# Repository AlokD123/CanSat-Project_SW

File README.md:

# README #

This is the flight software for the Carleton University CanSat team, primarily for the 2015 competition. Full details about the Int'l CanSat Competition may be found [here](http://www.cansatcompetition.com/). Note that the contents of this repository were migrated from a private Bitbucket repository which was used at the time of the competition, so author attributions are shown at the tops of files in lieu of a commit history.

### What is this repository for? ###

The Flight_SW directory contains all the required code to build and deploy the firmware for the CanSat Science Vehicle designed in 2014/2015. The GroundStation_SW directory contains the code to run a ground station GUI. The Flight_HW directory contains sample schematics, layouts, and images of PCBs designed for the competition.

### How do I get set up? ###

This software is written with CodeWarrior for MCUs (Special Edition). It is targeting a custom PCB with the MKL16Z.
In order to program the board in that IDE (not just debug it) you must go under Project->Properties->C/C++ Build->Settings->Librarian and change Model to ewl.

### Where can I find more details about the project? ###
Refer to the Critical Design Review (CDR) document: https://github.com/AlokD123/CanSat-Project_SW/blob/master/Cansat2015_1001_CDR_v01.pdf

For brevity, two concept images are shown below. The top image is the Concept of Operations for the competition. The bottom image is a block diagram of the can-sized satellite's electronics.

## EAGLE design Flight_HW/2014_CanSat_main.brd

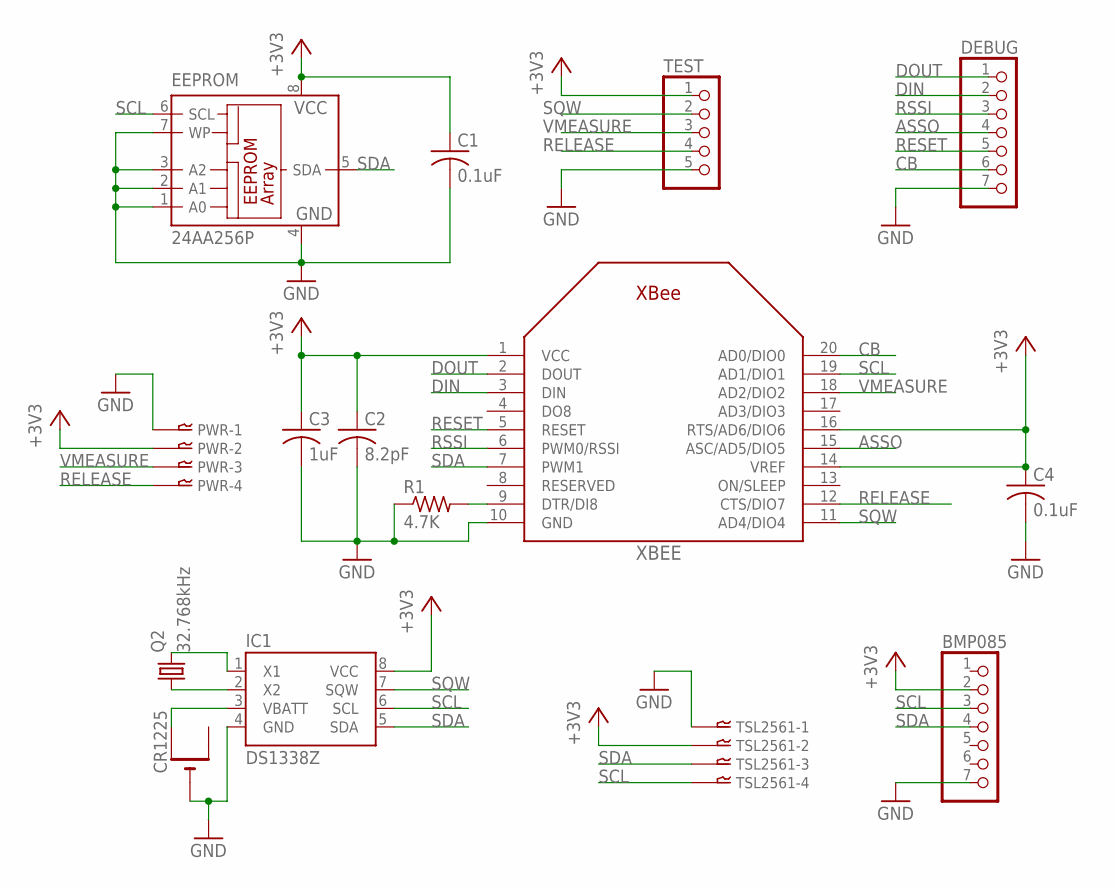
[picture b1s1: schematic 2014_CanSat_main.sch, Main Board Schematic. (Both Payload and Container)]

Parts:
BMP085: PINHD-1X7; 1X07
C1, C4: 0.1uF; C050-024X044
C2: 8.2pF; C050-024X044
C3: 1uF; C050-024X044
CR1225: CR1220THM; CR1220-THM
DEBUG: PINHD-1X7; 1X07
EEPROM: 24AA256P; DIL8
IC1: DS1338Z; SO08
PWR: 04-JST-B4B-XH-A; B4B-XH
Q2: 32.768kHz; TC26H
R1: 4.7K; 0309/10
TEST: PINHD-1X5; 1X05
TSL2561: 04-JST-B4B-XH-A; B4B-XH
XBEE: XBEE

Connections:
+3V3: BMP085.2, C1.1, C2.1, C3.1, C4.1, EEPROM.8 (VCC), IC1.8 (VCC), PWR.P$2, TEST.1, TSL2561.P$2, XBEE.1 (VCC), XBEE.14 (VREF), XBEE.16 (RTS/AD6/DIO6)
ASSO: DEBUG.4, XBEE.15 (ASC/AD5/DIO5)
CB: DEBUG.6, XBEE.20 (AD0/DIO0)
DIN: DEBUG.2, XBEE.3 (DIN)
DOUT: DEBUG.1, XBEE.2 (DOUT)
GND: BMP085.7, C1.2, C2.2, C3.2, C4.2, CR1225.-, DEBUG.7, EEPROM.1 (A0), EEPROM.2 (A1), EEPROM.3 (A2), EEPROM.4 (GND), EEPROM.7 (WP), IC1.4 (GND), PWR.P$1, R1.1, TEST.5, TSL2561.P$1, XBEE.10 (GND)
unnamed: R1.2, XBEE.9 (DTR/DI8)
unnamed: IC1.2 (X2), Q2.1
unnamed: IC1.1 (X1), Q2.2
unnamed: CR1225.+1 (+), IC1.3 (VBATT)
RELEASE: PWR.P$4, TEST.4, XBEE.12 (CTS/DIO7)
RESET: DEBUG.5, XBEE.5 (RESET)
RSSI: DEBUG.3, XBEE.6 (PWM0/RSSI)
SCL: BMP085.3, EEPROM.6 (SCL), IC1.6 (SCL), TSL2561.P$4, XBEE.19 (AD1/DIO1)
SDA: BMP085.4, EEPROM.5 (SDA), IC1.5 (SDA), TSL2561.P$3, XBEE.7 (PWM1)
SQW: IC1.7 (SQW), TEST.2, XBEE.11 (AD4/DIO4)
VMEASURE: PWR.P$3, TEST.3, XBEE.18 (AD2/DIO2)

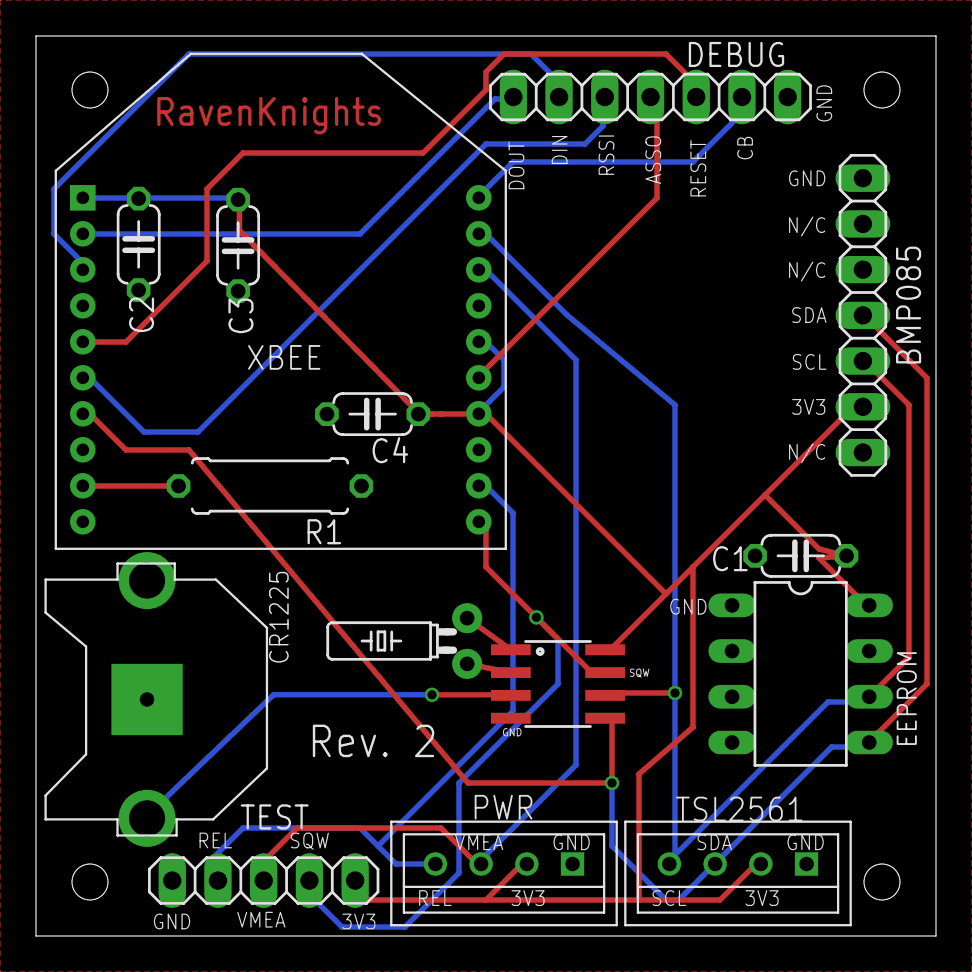
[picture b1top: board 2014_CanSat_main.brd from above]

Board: 2 copper layers, 50.0 x 50.0 mm, 15 parts (0 on the bottom side), 17 nets.

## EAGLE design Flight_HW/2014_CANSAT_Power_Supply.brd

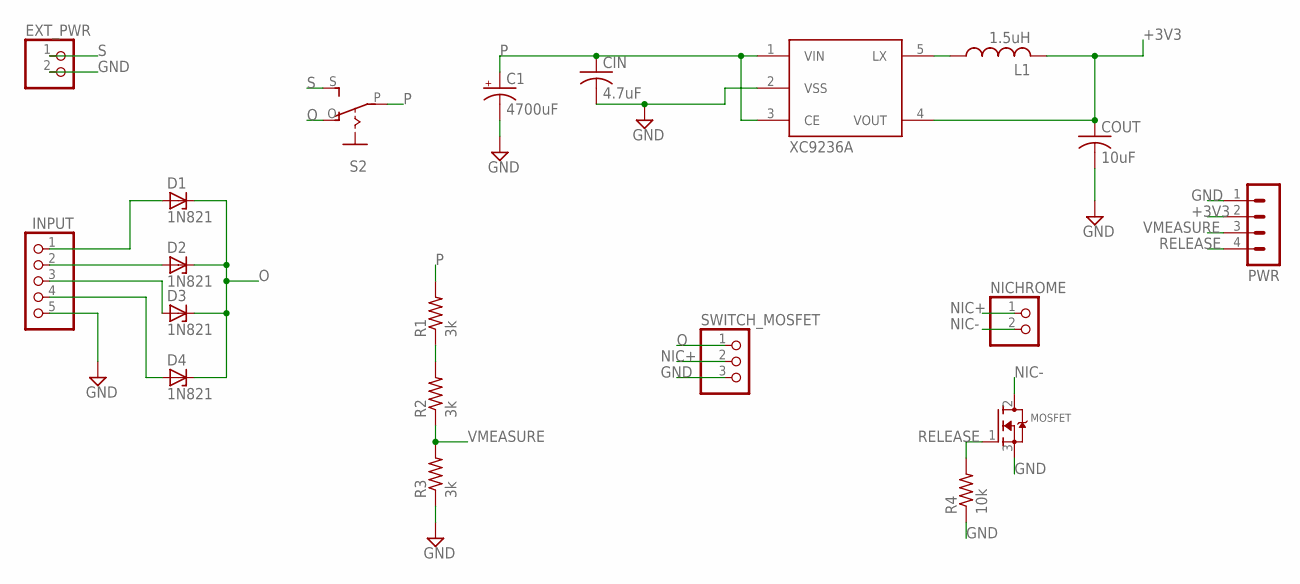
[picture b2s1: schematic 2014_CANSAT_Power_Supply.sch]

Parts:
C1: 4700uF; E5-5
CIN: 4.7uF; C050-024X044
COUT: 10uF; C050-024X044
D1, D2, D3, D4: 1N821; DO35Z10
EXT_PWR: PINHD-1X2; 1X02
INPUT: PINHD-1X5; 1X05
L1: 1.5uH; 6000-XXXX-RC
MOSFET: MOSFET-NGDS_TO220V; TO220V
NICHROME: PINHD-1X2; 1X02
PWR: MA04-1
R1, R2, R3: 3k; 0309/10
R4: 10k; 0309/10
S2: EG1218S; EG1218
SWITCH_MOSFET: PINHD-1X3; 1X03
XC9236A: MCP73811/2; SOT23-5L

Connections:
+3V3: COUT.1, L1.2, PWR.2, XC9236A.4 (VOUT)
GND: C1.-, CIN.2, COUT.2, EXT_PWR.2, INPUT.5, MOSFET.3 (S), PWR.1, R3.1, R4.1, SWITCH_MOSFET.3, XC9236A.2 (VSS)
unnamed: R1.1, R2.2
unnamed: D1.A, INPUT.1
unnamed: D2.A, INPUT.2
unnamed: D3.A, INPUT.3
unnamed: L1.1, XC9236A.5 (LX)
unnamed: D4.A, INPUT.4
NIC+: NICHROME.1, SWITCH_MOSFET.2
NIC-: MOSFET.2 (D), NICHROME.2
O: D1.C, D2.C, D3.C, D4.C, S2.O, SWITCH_MOSFET.1
P: C1.+, CIN.1, R1.2, S2.P, XC9236A.1 (VIN), XC9236A.3 (CE)
RELEASE: MOSFET.1 (G), PWR.4, R4.2
S: EXT_PWR.1, S2.S
VMEASURE: PWR.3, R2.1, R3.2

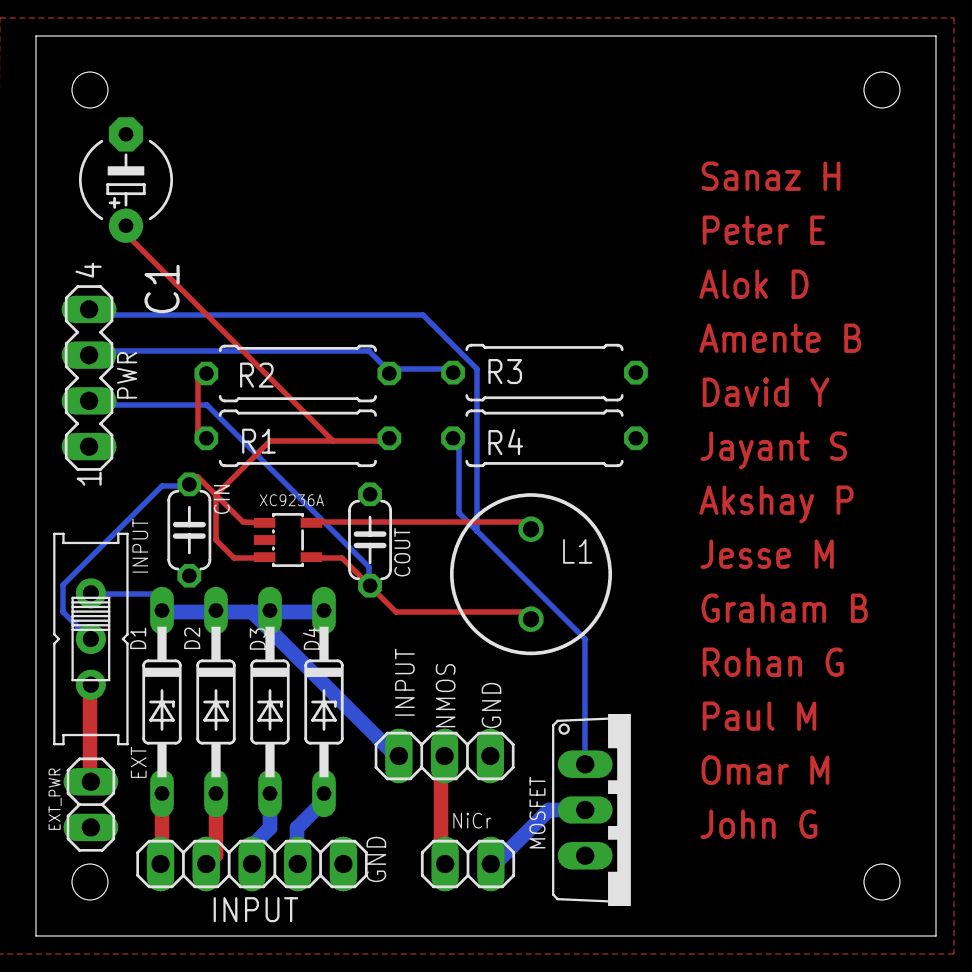
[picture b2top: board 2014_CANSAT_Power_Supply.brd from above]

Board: 2 copper layers, 50.0 x 50.0 mm, 20 parts (0 on the bottom side), 15 nets.

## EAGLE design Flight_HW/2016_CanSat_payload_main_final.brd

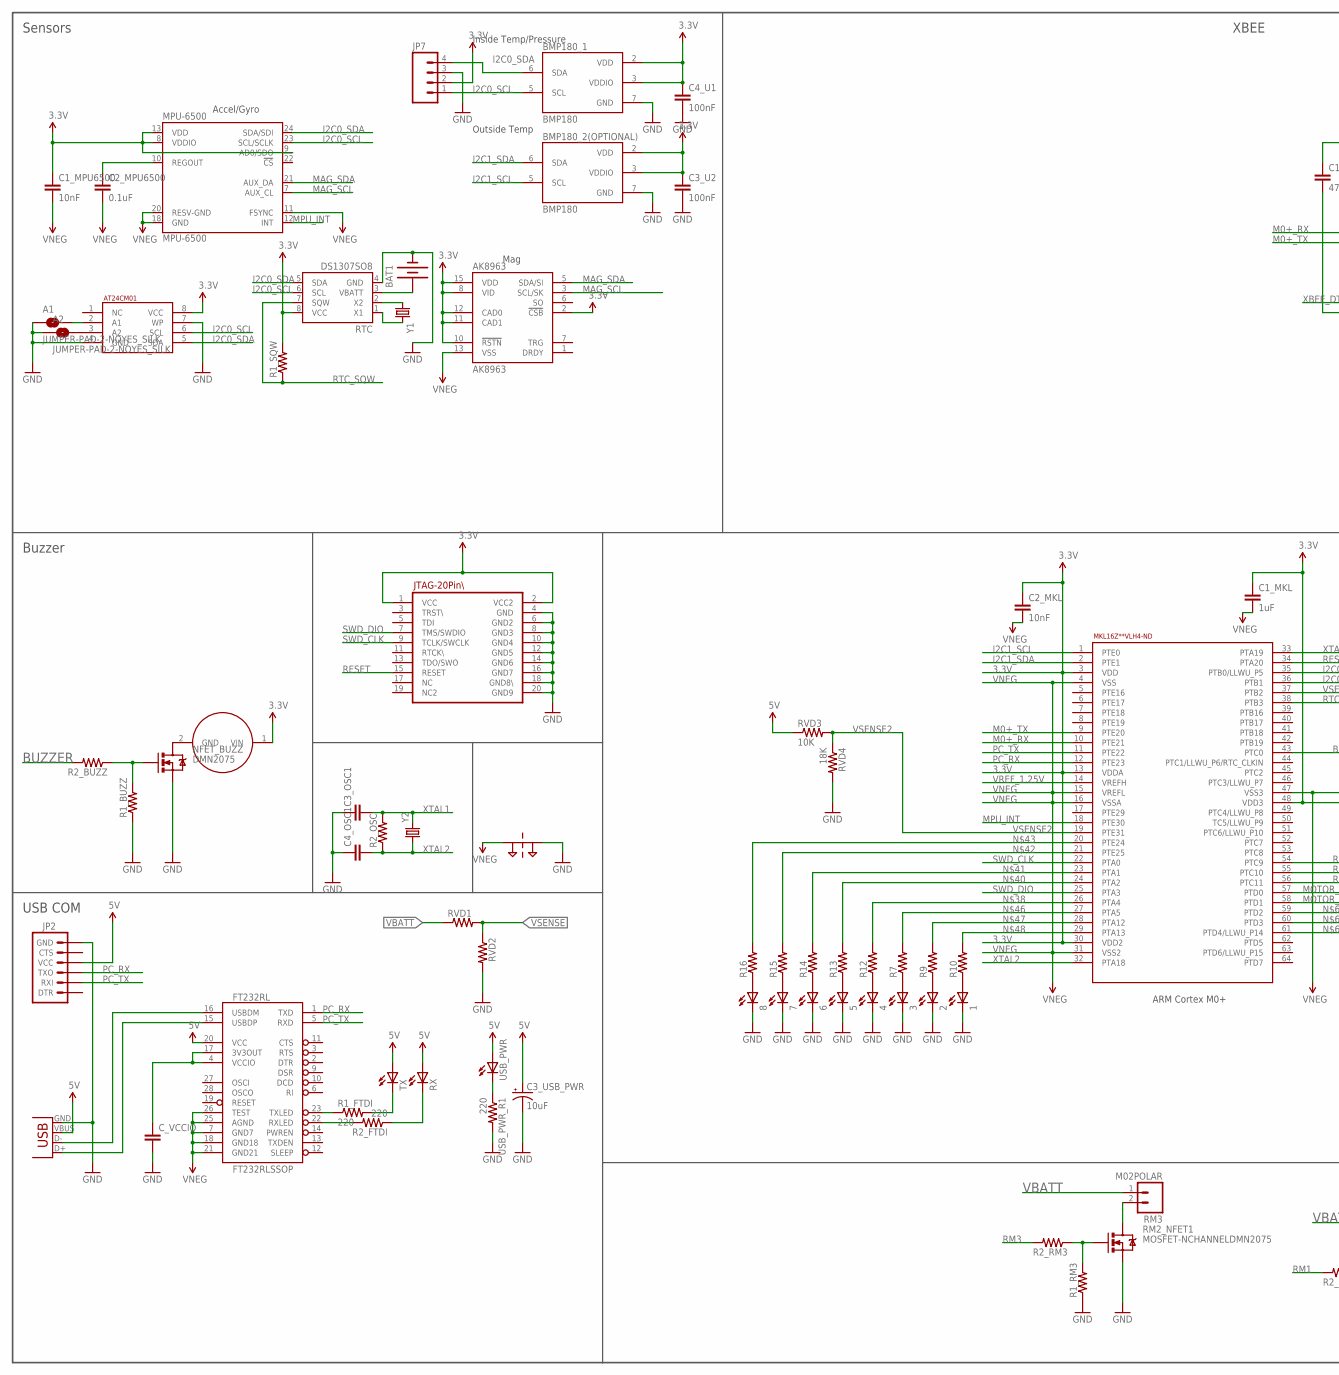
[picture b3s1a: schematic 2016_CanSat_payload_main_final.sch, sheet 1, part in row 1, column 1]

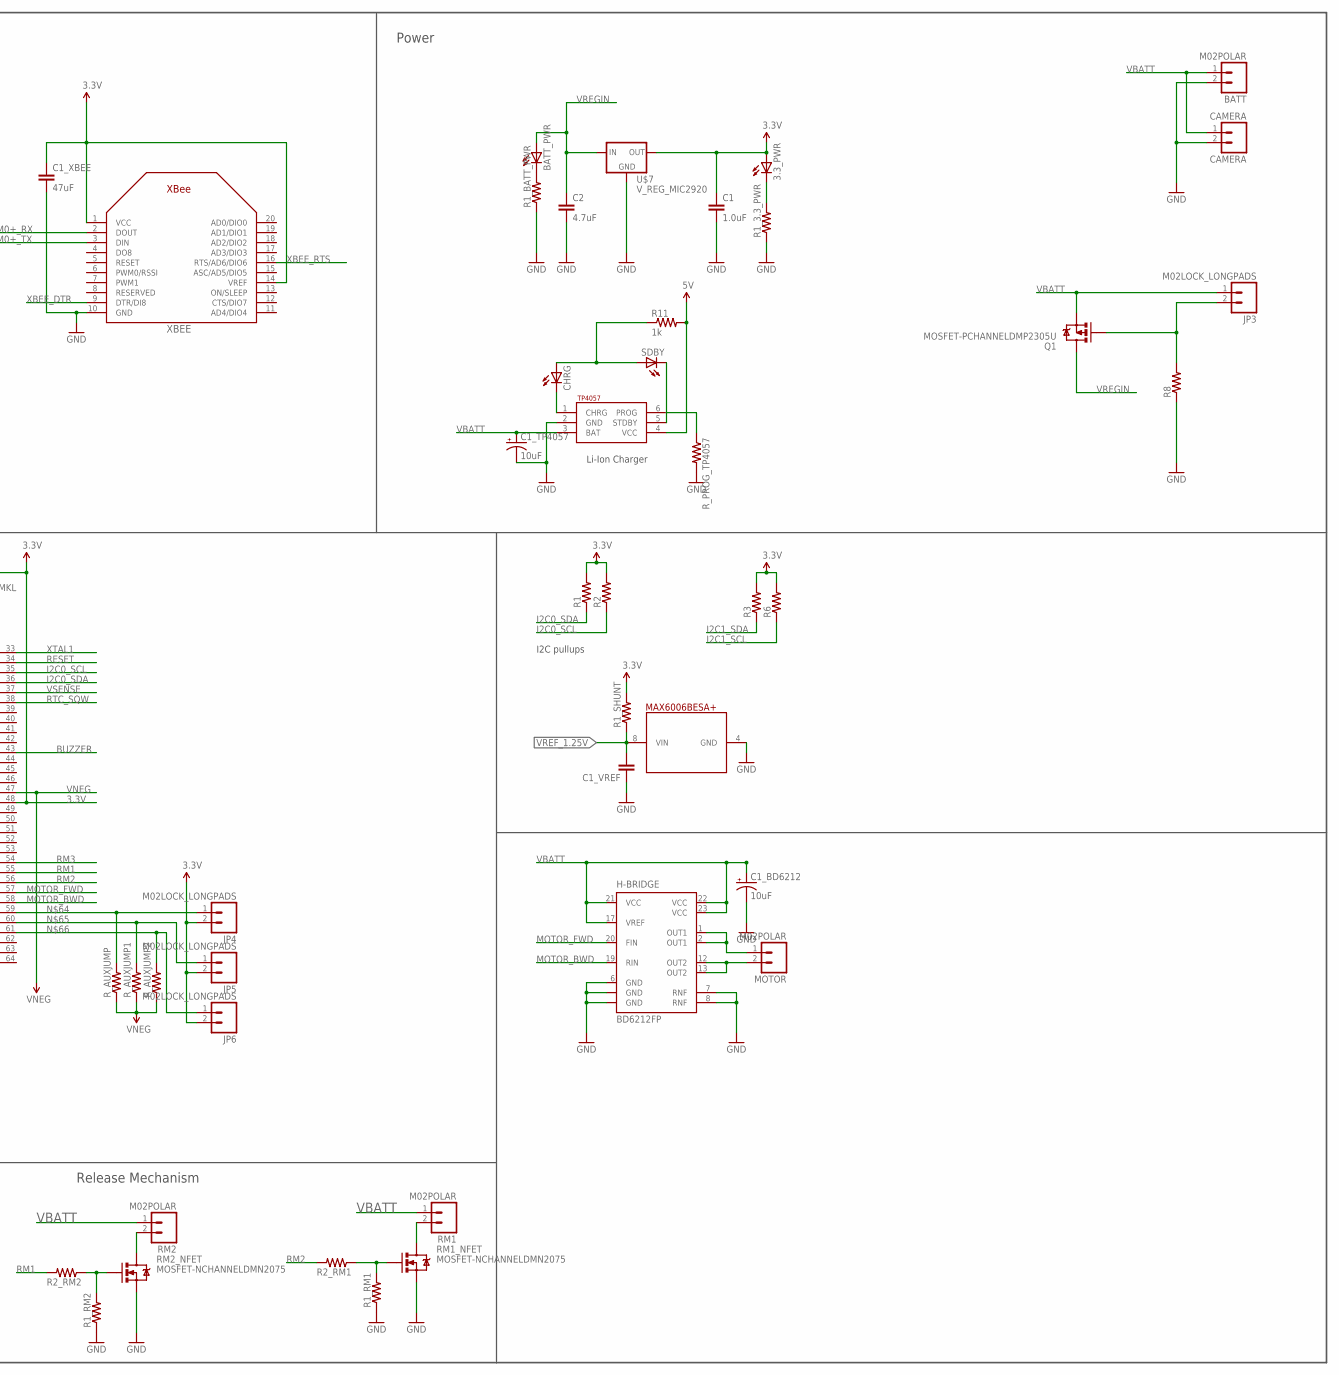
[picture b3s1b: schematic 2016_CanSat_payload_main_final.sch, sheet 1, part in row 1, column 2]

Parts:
1, 2, 3, 3.3_PWR, 4, 5, 6, 7, 8: LEDCHIP-LED0603; CHIP-LED0603
A1, A2: JUMPER-PAD-2-NOYES_SILK; PAD-JUMPER-2-NO_YES_SILK
AK8963: AK8963; QFN16-HS
BAT1: BATTERY12MM; BATTCON_12MM
BATT: M02POLAR; MOLEX-1X2
BATT_PWR: LEDCHIP-LED0603; CHIP-LED0603
BMP180_1, BMP180_2(OPTIONAL): BMP180
C1: 1.0uF; 0603-CAP
C1_BD6212, C1_TP4057, C3_USB_PWR: 10uF; EIA3216
C1_MKL: 1uF; 0603-CAP
C1_MPU6500, C2_MKL: 10nF; 0603-CAP
C1_VREF, C3_OSC1, C4_OSC1: CAP0603-CAP; 0603-CAP
C1_XBEE: 47uF; 0603-CAP
C2: 4.7uF; 0603-CAP
C2_MPU6500: 0.1uF; 0603-CAP
C3_U2, C4_U1: 100nF; 0603-CAP
CAMERA: CAMERA; MOLEX-1X2
CHRG: LEDCHIPLED_0603; CHIPLED_0603
C_VCCIO: CAP0603-CAP; 0603-CAP
FT232RL: FT232RLSSOP; SSOP28DB
H-BRIDGE: BD6212FP; HSOP25
JP1: USBOLD; USB-MINIB-OLD
JP2: ARDUINO_SERIAL_PROGRAMLONGPADS; 1X06_LONGPADS
JP3, JP4, JP5, JP6: M02LOCK_LONGPADS; 1X02_LOCK_LONGPADS
JP7: M04POLAR; MOLEX-1X4
JTAG: JTAG_20PIN; 2X10
MKL16: MKL16ZVLH4-ND; TQFP64
MOTOR: M02POLAR; MOLEX-1X2
MPU-6500: MPU-6500; QFN-24
NFET_BUZZ: DMN2075; SOT23
PT1: 2PT_GND_TIE
Q1: MOSFET-PCHANNELDMP2305U; SOT23-3
R1, R1_SQW, R2, R3, R6, R7, R9, R10, R12, R13, R14, R15, R16: RESISTOR0603-RES; 0603-RES
R1_3.3_PWR, R1_BATT_PWR, R8: RESISTOR0603; 0603-RES
R1_BUZZ, R1_RM1, R1_RM2, R1_RM3, R1_SHUNT, R2_BUZZ, R2_OSC, R2_RM1, R2_RM2, R2_RM3: RESISTOR0805-RES; 0805
R1_FTDI, R2_FTDI: 220; 0603-RES
R11: 1k; 0603-RES
RM1, RM2, RM3: M02POLAR; MOLEX-1X2
RM1_NFET, RM2_NFET, RM2_NFET1: MOSFET-NCHANNELDMN2075; SOT23
RTC: DS1307SO8; SO08
RVD1, RVD2: RESISTOR0805-RES; 0805
RVD3: 10K; 0805
RVD4: 18K; 0805
RX: LEDCHIPLED_0603; CHIPLED_0603
R_AUXJUMP, R_AUXJUMP1, R_AUXJUMP2: RESISTOR0805-RES; 0805
R_PROG_TP4057: RESISTOR0603; 0603-RES
SDBY: LEDCHIPLED_0603; CHIPLED_0603
TX: LEDCHIPLED_0603; CHIPLED_0603
U$2: AT24CM01; SO08
U$3: TP4057; SOT23-6
U$4: AI-1027-TWT-3V-R_BUZZER
U$5: MAX6006BESA+; SO08
U$7: V_REG_MIC2920; SOT223
USB_PWR: LEDCHIPLED_0603; CHIPLED_0603
USB_PWR_R1: 220; 0603-RES
XBEE: XBEE
Y1: CRYSTAL32-SMD; CRYSTAL-32KHZ-SMD
Y2: CRYSTAL5X3; CRYSTAL-SMD-5X3

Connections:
3.3V: 3.3_PWR.A, AK8963.2 (!CSB), AK8963.8 (VID), AK8963.10 (!RSTN), AK8963.11 (CAD1), AK8963.12 (CAD0), AK8963.15 (VDD), BMP180_1.2 (VDD), BMP180_1.3 (VDDIO), BMP180_2(OPTIONAL).2 (VDD), BMP180_2(OPTIONAL).3 (VDDIO), C1.1, C1_MKL.1, C1_MPU6500.1, C1_XBEE.1, C2_MKL.1, C3_U2.1, C4_U1.1, JP4.2, JP5.2, JP6.2, JP7.2, JTAG.1 (VCC), JTAG.2 (VCC2), MKL16.3 (VDD), MKL16.13 (VDDA), MKL16.30 (VDD2), MKL16.48 (VDD3), MPU-6500.8 (VDDIO), MPU-6500.9 (AD0/SDO), MPU-6500.13 (VDD), R1.2, R1_SHUNT.2, R1_SQW.2, R2.2, R3.2, R6.2, RTC.8 (VCC), U$2.8 (VCC), U$4.1 (VIN), U$7.3 (OUT), XBEE.1 (VCC), XBEE.14 (VREF)
5V: C3_USB_PWR.A (+), FT232RL.20 (VCC), JP1.VBUS, JP2.4 (VCC), R11.2, RVD3.1, RX.A, TX.A, U$3.4 (VCC), USB_PWR.A
BUZZER: MKL16.43 (PTC0), R2_BUZZ.2
GND: 1.C, 2.C, 3.C, 4.C, 5.C, 6.C, 7.C, 8.C, A1.1, A2.1, BAT1.GND (-), BATT.2, BMP180_1.7 (GND), BMP180_2(OPTIONAL).7 (GND), C1.2, C1_BD6212.C (-), C1_TP4057.C (-), C1_VREF.1, C1_XBEE.2, C2.2, C3_OSC1.1, C3_U2.2, C3_USB_PWR.C (-), C4_OSC1.1, C4_U1.2, CAMERA.2, C_VCCIO.2, H-BRIDGE.6 (GND), H-BRIDGE.7 (RNF), H-BRIDGE.8 (RNF), H-BRIDGE.GND@1 (GND), H-BRIDGE.GND@2 (GND), JP1.GND, JP2.6 (GND), JP7.3, JTAG.4 (GND), JTAG.6 (GND2), JTAG.8 (GND3), JTAG.10 (GND4), JTAG.12 (GND5), JTAG.14 (GND6), JTAG.16 (GND7), JTAG.18 (GND8\), JTAG.20 (GND9), NFET_BUZZ.2 (S), PT1.P$2, R1_3.3_PWR.1, R1_BATT_PWR.1, R1_BUZZ.1, R1_RM1.1, R1_RM2.1, R1_RM3.1, R8.1, RM1_NFET.2 (S), RM2_NFET.2 (S), RM2_NFET1.2 (S), RTC.4 (GND), RVD2.2, RVD4.2, R_PROG_TP4057.2, U$2.4 (GND), U$2.7 (WP), U$3.2 (GND), U$5.4 (GND), U$7.2 (GND), USB_PWR_R1.2, XBEE.10 (GND)
I2C0_SCL: BMP180_1.5 (SCL), JP7.1, MKL16.35 (PTB0/LLWU_P5), MPU-6500.23 (SCL/SCLK), R2.1, RTC.6 (SCL), U$2.6 (SCL)
I2C0_SDA: BMP180_1.6 (SDA), JP7.4, MKL16.36 (PTB1), MPU-6500.24 (SDA/SDI), R1.1, RTC.5 (SDA), U$2.5 (SDA)
I2C1_SCL: BMP180_2(OPTIONAL).5 (SCL), MKL16.1 (PTE0), R6.1
I2C1_SDA: BMP180_2(OPTIONAL).6 (SDA), MKL16.2 (PTE1), R3.1
M0+_RX: MKL16.10 (PTE21), XBEE.2 (DOUT)
M0+_TX: MKL16.9 (PTE20), XBEE.3 (DIN)
MAG_SCL: AK8963.3 (SCL/SK), MPU-6500.7 (AUX_CL)
MAG_SDA: AK8963.5 (SDA/SI), MPU-6500.21 (AUX_DA)
MOTOR_BWD: H-BRIDGE.19 (RIN), MKL16.58 (PTD1)
MOTOR_FWD: H-BRIDGE.20 (FIN), MKL16.57 (PTD0)
MPU_INT: MKL16.18 (PTE30), MPU-6500.12 (INT)
unnamed: 3.A, R7.1
unnamed: 1.A, R10.1
unnamed: FT232RL.16 (USBDM), JP1.D-
unnamed: C2_MPU6500.1, MPU-6500.10 (REGOUT)
unnamed: FT232RL.15 (USBDP), JP1.D+
unnamed: FT232RL.23 (TXLED), R1_FTDI.1
unnamed: A2.2, U$2.3 (A2)
unnamed: R1_FTDI.2, TX.C
unnamed: FT232RL.22 (RXLED), R2_FTDI.2
unnamed: R2_FTDI.1, RX.C
unnamed: USB_PWR.C, USB_PWR_R1.1
unnamed: C_VCCIO.1, FT232RL.4 (VCCIO), FT232RL.17 (3V3OUT)
unnamed: A1.2, U$2.2 (A1)
unnamed: JP3.2, Q1.1 (G), R8.2
unnamed: 3.3_PWR.C, R1_3.3_PWR.2
unnamed: BATT_PWR.C, R1_BATT_PWR.2
unnamed: CHRG.A, R11.1, SDBY.A
unnamed: CHRG.C, U$3.1 (CHRG)
unnamed: SDBY.C, U$3.5 (STDBY)
unnamed: R_PROG_TP4057.1, U$3.6 (PROG)
unnamed: NFET_BUZZ.1 (G), R1_BUZZ.2, R2_BUZZ.1
unnamed: 2.A, R9.1
unnamed: R1_RM1.2, R2_RM1.1, RM1_NFET.1 (G)
unnamed: H-BRIDGE.1 (OUT1), H-BRIDGE.2 (OUT1), MOTOR.1
unnamed: NFET_BUZZ.3 (D), U$4.2 (GND)
unnamed: 8.A, R16.1
unnamed: RM2.2, RM2_NFET.3 (D)
unnamed: H-BRIDGE.12 (OUT2), H-BRIDGE.13 (OUT2), MOTOR.2
unnamed: RTC.2 (X2), Y1.X1 (1)
unnamed: RTC.1 (X1), Y1.X2 (2)
unnamed: BAT1.PWR@1 (+), RTC.3 (VBATT)
unnamed: MKL16.26 (PTA4), R12.2
unnamed: RM1.2, RM1_NFET.3 (D)
unnamed: MKL16.24 (PTA2), R13.2
unnamed: MKL16.23 (PTA1), R14.2
unnamed: MKL16.21 (PTE25), R15.2
unnamed: MKL16.20 (PTE24), R16.2
unnamed: RM2_NFET1.3 (D), RM3.2
unnamed: MKL16.27 (PTA5), R7.2
unnamed: MKL16.28 (PTA12), R9.2
unnamed: MKL16.29 (PTA13), R10.2
unnamed: 4.A, R12.1
unnamed: JP4.1, MKL16.59 (PTD2), R_AUXJUMP.2
unnamed: JP5.1, MKL16.60 (PTD3), R_AUXJUMP1.2
unnamed: JP6.1, MKL16.61 (PTD4/LLWU_P14), R_AUXJUMP2.2
unnamed: 5.A, R13.1
unnamed: 6.A, R14.1
unnamed: 7.A, R15.1
PC_RX: FT232RL.1 (TXD), JP2.3 (TXO), MKL16.12 (PTE23)
PC_TX: FT232RL.5 (RXD), JP2.2 (RXI), MKL16.11 (PTE22)
R2_RM1: R1_RM3.2, R2_RM3.1, RM2_NFET1.1 (G)
R2_RM2: R1_RM2.2, R2_RM2.1, RM2_NFET.1 (G)
RESET: JTAG.15 (RESET), MKL16.34 (PTA20)
RM1: MKL16.55 (PTC10), R2_RM2.2
RM2: MKL16.56 (PTC11), R2_RM1.2
RM3: MKL16.54 (PTC9), R2_RM3.2
RTC_SQW: MKL16.38 (PTB3), R1_SQW.1, RTC.7 (SQW)
SWD_CLK: JTAG.9 (TCLK/SWCLK), MKL16.22 (PTA0)
SWD_DIO: JTAG.7 (TMS/SWDIO), MKL16.25 (PTA3)
VBATT: BATT.1, C1_BD6212.A (+), C1_TP4057.A (+), CAMERA.1, H-BRIDGE.17 (VREF), H-BRIDGE.21 (VCC), H-BRIDGE.22 (VCC), H-BRIDGE.23 (VCC), JP3.1, Q1.2 (S), RM1.1, RM2.1, RM3.1, RVD1.1, U$3.3 (BAT)
VNEG: AK8963.13 (VSS), C1_MKL.2, C1_MPU6500.2, C2_MKL.2, C2_MPU6500.2, FT232RL.7 (GND7), FT232RL.18 (GND18), FT232RL.21 (GND21), FT232RL.25 (AGND), FT232RL.26 (TEST), MKL16.4 (VSS), MKL16.15 (VREFL), MKL16.16 (VSSA), MKL16.31 (VSS2), MKL16.47 (VSS3), MPU-6500.11 (FSYNC), MPU-6500.18 (GND), MPU-6500.20 (RESV-GND), PT1.P$1, R_AUXJUMP.1, R_AUXJUMP1.1, R_AUXJUMP2.1
VREF_1.25V: C1_VREF.2, MKL16.14 (VREFH), R1_SHUNT.1, U$5.8 (VIN)
VREGIN: BATT_PWR.A, C2.1, Q1.3 (D), U$7.1 (IN)
VSENSE: MKL16.37 (PTB2), RVD1.2, RVD2.1
VSENSE2: MKL16.19 (PTE31), RVD3.2, RVD4.1
XBEE_DTR: XBEE.9 (DTR/DI8)
XBEE_RTS: XBEE.16 (RTS/AD6/DIO6)
XTAL1: C3_OSC1.2, MKL16.33 (PTA19), R2_OSC.2, Y2.3 (2)
XTAL2: C4_OSC1.2, MKL16.32 (PTA18), R2_OSC.1, Y2.1

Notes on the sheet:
Sensors
Power
XBEE
I2C pullups
Inside Temp/Pressure
Outside Temp
Accel/Gyro
Mag
USB COM
Buzzer
Li-Ion Charger
ARM Cortex M0+
Release Mechanism

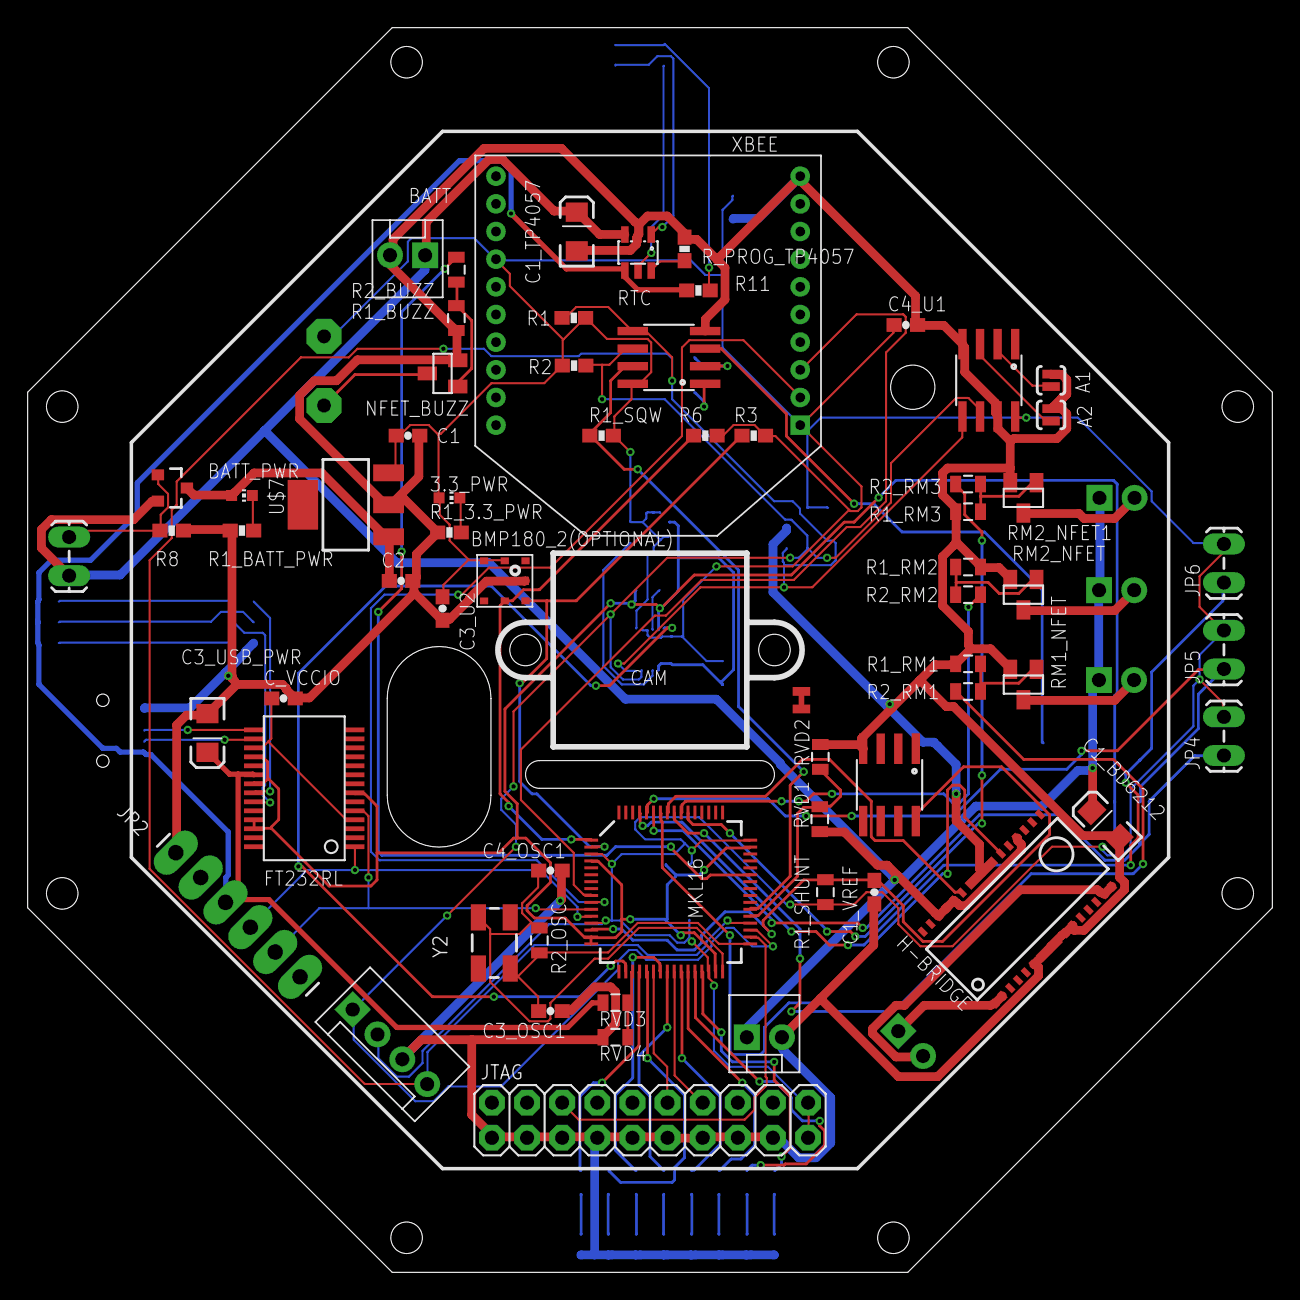
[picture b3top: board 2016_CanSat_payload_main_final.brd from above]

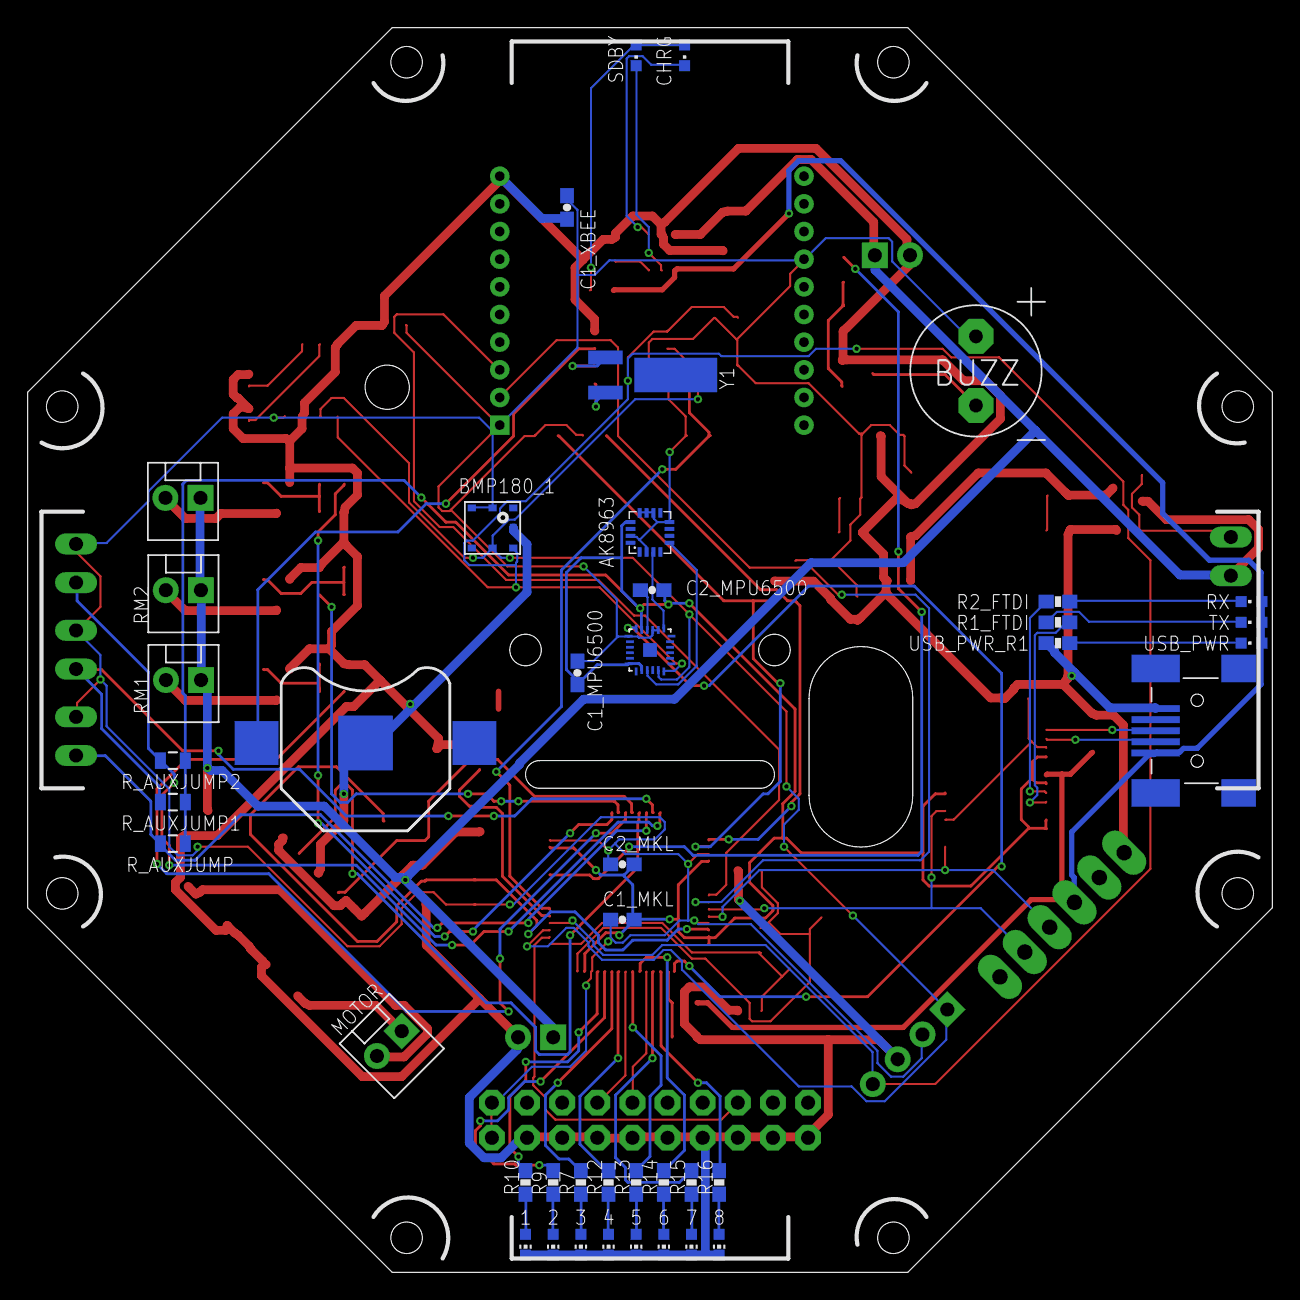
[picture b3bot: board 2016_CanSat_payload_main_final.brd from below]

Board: 2 copper layers, 90.0 x 90.0 mm, 108 parts (43 on the bottom side), 82 nets.

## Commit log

2019-12-03 Migrated project from Bitbucket.
2020-07-31 Added HW PCB designs, as well as full system design images

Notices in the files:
parts and their libraries:
SparkFun-Sensors: Licensing: Creative Commons ShareAlike 4.0 International - https://creativecommons.org/licenses/by-sa/4.0
